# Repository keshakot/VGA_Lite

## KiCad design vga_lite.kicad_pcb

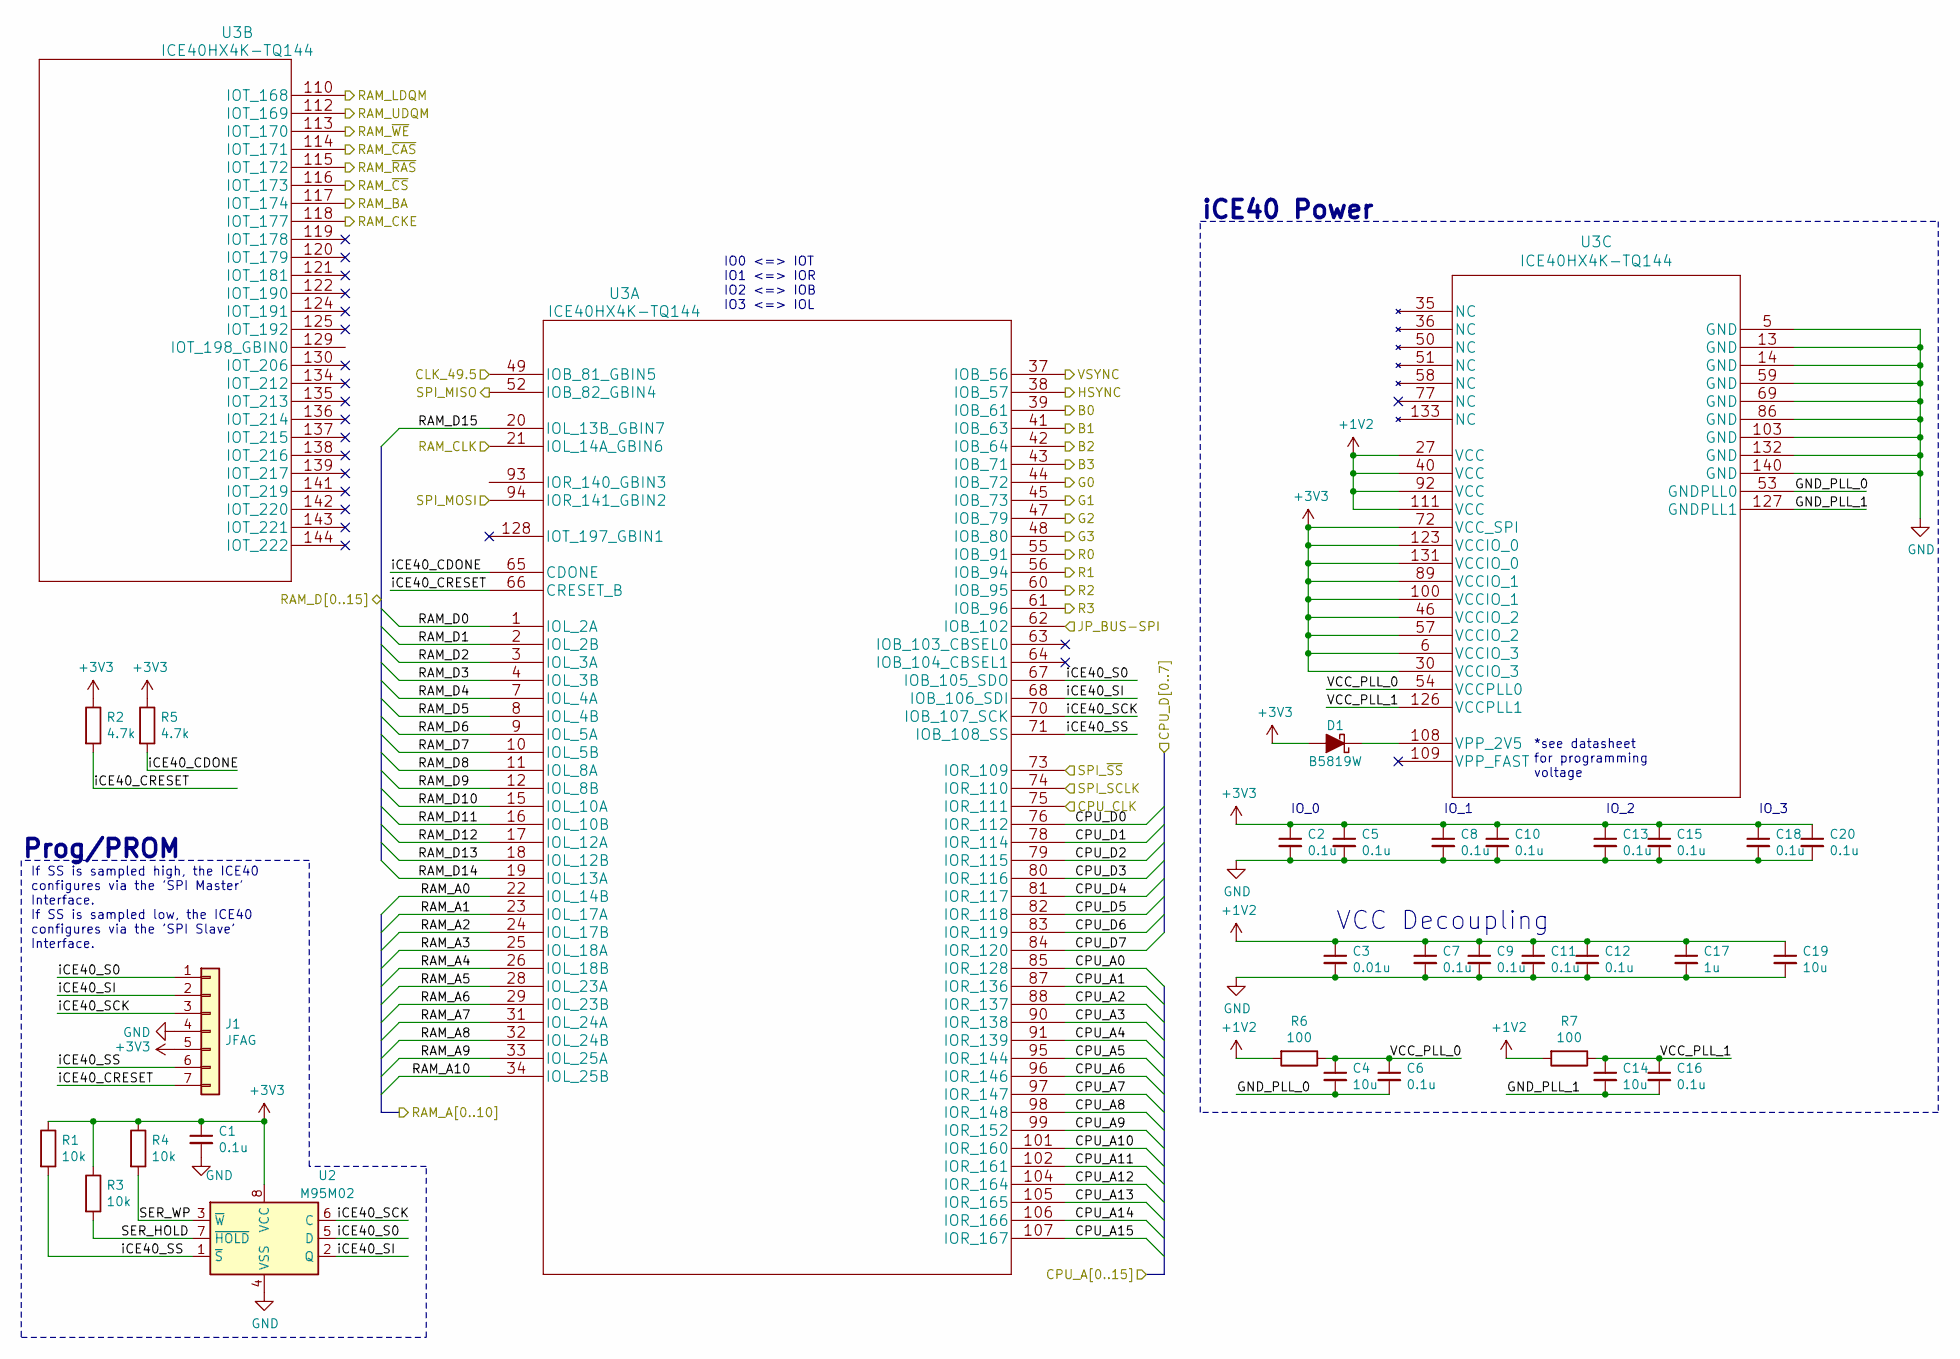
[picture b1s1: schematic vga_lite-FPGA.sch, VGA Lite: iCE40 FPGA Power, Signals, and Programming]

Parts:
C1, C2, C5, C6, C7, C8, C9, C10, C11, C12, C13, C15, C16, C18, C20: 0.1u; C_0402_1005Metric
C3: 0.01u; C_0402_1005Metric
C4, C14, C19: 10u; C_0402_1005Metric
C17: 1u; C_0402_1005Metric
D1: B5819W; D_SOD-123
J1: JFAG; PinHeader_1x07_P2.54mm_Vertical
R1, R3, R4: 10k; R_0402_1005Metric
R2, R5: 4.7k; R_0402_1005Metric
R6, R7: 100; R_0402_1005Metric
U2: M95M02; SOIC-8_3.9x4.9mm_P1.27mm
U3: ICE40HX4K-TQ144; TQFP-144_20x20mm_P0.5mm

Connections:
+1V2: C3.1, C7.1, C9.1, C11.1, C12.1, C17.1, C19.1, R6.2, R7.2, U3.27 (VCC), U3.40 (VCC), U3.92 (VCC), U3.111 (VCC); also elsewhere on the board
/FPGA/B0: U3.39 (IOB_61); also elsewhere on the board
/FPGA/B1: U3.41 (IOB_63); also elsewhere on the board
/FPGA/B2: U3.42 (IOB_64); also elsewhere on the board
/FPGA/B3: U3.43 (IOB_71); also elsewhere on the board
/FPGA/CLK_49.5: U3.49 (IOB_81_GBIN5); also elsewhere on the board
/FPGA/CPU_A0: U3.85 (IOR_128); also elsewhere on the board
/FPGA/CPU_A1: U3.87 (IOR_136); also elsewhere on the board
/FPGA/CPU_A2: U3.88 (IOR_137); also elsewhere on the board
/FPGA/CPU_A3: U3.90 (IOR_138); also elsewhere on the board
/FPGA/CPU_A4: U3.91 (IOR_139); also elsewhere on the board
/FPGA/CPU_A5: U3.95 (IOR_144); also elsewhere on the board
/FPGA/CPU_A6: U3.96 (IOR_146); also elsewhere on the board
/FPGA/CPU_A7: U3.97 (IOR_147); also elsewhere on the board
/FPGA/CPU_A8: U3.98 (IOR_148); also elsewhere on the board
/FPGA/CPU_A9: U3.99 (IOR_152); also elsewhere on the board
/FPGA/CPU_A10: U3.101 (IOR_160); also elsewhere on the board
/FPGA/CPU_A11: U3.102 (IOR_161); also elsewhere on the board
/FPGA/CPU_A12: U3.104 (IOR_164); also elsewhere on the board
/FPGA/CPU_A13: U3.105 (IOR_165); also elsewhere on the board
/FPGA/CPU_A14: U3.106 (IOR_166); also elsewhere on the board
/FPGA/CPU_A15: U3.107 (IOR_167); also elsewhere on the board
/FPGA/CPU_CLK: U3.75 (IOR_111); also elsewhere on the board
/FPGA/CPU_D0: U3.76 (IOR_112); also elsewhere on the board
/FPGA/CPU_D1: U3.78 (IOR_114); also elsewhere on the board
/FPGA/CPU_D2: U3.79 (IOR_115); also elsewhere on the board
/FPGA/CPU_D3: U3.80 (IOR_116); also elsewhere on the board
/FPGA/CPU_D4: U3.81 (IOR_117); also elsewhere on the board
/FPGA/CPU_D5: U3.82 (IOR_118); also elsewhere on the board
/FPGA/CPU_D6: U3.83 (IOR_119); also elsewhere on the board
/FPGA/CPU_D7: U3.84 (IOR_120); also elsewhere on the board
/FPGA/G0: U3.44 (IOB_72); also elsewhere on the board
/FPGA/G1: U3.45 (IOB_73); also elsewhere on the board
/FPGA/G2: U3.47 (IOB_79); also elsewhere on the board
/FPGA/G3: U3.48 (IOB_80); also elsewhere on the board
/FPGA/GND_PLL_0: C4.2, C6.2, U3.53 (GNDPLL0)
/FPGA/GND_PLL_1: C14.2, C16.2, U3.127 (GNDPLL1)
/FPGA/HSYNC: U3.38 (IOB_57); also elsewhere on the board
/FPGA/JP_BUS-SPI: U3.62 (IOB_102); also elsewhere on the board
/FPGA/R0: U3.55 (IOB_91); also elsewhere on the board
/FPGA/R1: U3.56 (IOB_94); also elsewhere on the board
/FPGA/R2: U3.60 (IOB_95); also elsewhere on the board
/FPGA/R3: U3.61 (IOB_96); also elsewhere on the board
/FPGA/RAM_A0: U3.22 (IOL_14B); also elsewhere on the board
/FPGA/RAM_A1: U3.23 (IOL_17A); also elsewhere on the board
/FPGA/RAM_A2: U3.24 (IOL_17B); also elsewhere on the board
/FPGA/RAM_A3: U3.25 (IOL_18A); also elsewhere on the board
/FPGA/RAM_A4: U3.26 (IOL_18B); also elsewhere on the board
/FPGA/RAM_A5: U3.28 (IOL_23A); also elsewhere on the board
/FPGA/RAM_A6: U3.29 (IOL_23B); also elsewhere on the board
/FPGA/RAM_A7: U3.31 (IOL_24A); also elsewhere on the board
/FPGA/RAM_A8: U3.32 (IOL_24B); also elsewhere on the board
/FPGA/RAM_A9: U3.33 (IOL_25A); also elsewhere on the board
/FPGA/RAM_A10: U3.34 (IOL_25B); also elsewhere on the board
/FPGA/RAM_BA: U3.117 (IOT_174); also elsewhere on the board
/FPGA/RAM_CKE: U3.118 (IOT_177); also elsewhere on the board
/FPGA/RAM_CLK: U3.21 (IOL_14A_GBIN6); also elsewhere on the board
/FPGA/RAM_D0: U3.1 (IOL_2A); also elsewhere on the board
/FPGA/RAM_D1: U3.2 (IOL_2B); also elsewhere on the board
/FPGA/RAM_D2: U3.3 (IOL_3A); also elsewhere on the board
/FPGA/RAM_D3: U3.4 (IOL_3B); also elsewhere on the board
/FPGA/RAM_D4: U3.7 (IOL_4A); also elsewhere on the board
/FPGA/RAM_D5: U3.8 (IOL_4B); also elsewhere on the board
/FPGA/RAM_D6: U3.9 (IOL_5A); also elsewhere on the board
/FPGA/RAM_D7: U3.10 (IOL_5B); also elsewhere on the board
/FPGA/RAM_D8: U3.11 (IOL_8A); also elsewhere on the board
/FPGA/RAM_D9: U3.12 (IOL_8B); also elsewhere on the board
/FPGA/RAM_D10: U3.15 (IOL_10A); also elsewhere on the board
/FPGA/RAM_D11: U3.16 (IOL_10B); also elsewhere on the board
/FPGA/RAM_D12: U3.17 (IOL_12A); also elsewhere on the board
/FPGA/RAM_D13: U3.18 (IOL_12B); also elsewhere on the board
/FPGA/RAM_D14: U3.19 (IOL_13A); also elsewhere on the board
/FPGA/RAM_D15: U3.20 (IOL_13B_GBIN7); also elsewhere on the board
/FPGA/RAM_LDQM: U3.110 (IOT_168); also elsewhere on the board
/FPGA/RAM_UDQM: U3.112 (IOT_169); also elsewhere on the board
/FPGA/RAM_~CAS: U3.114 (IOT_171); also elsewhere on the board
/FPGA/RAM_~CS: U3.116 (IOT_173); also elsewhere on the board
/FPGA/RAM_~RAS: U3.115 (IOT_172); also elsewhere on the board
/FPGA/RAM_~WE: U3.113 (IOT_170); also elsewhere on the board
/FPGA/SER_HOLD: R3.2, U2.7 (~HOLD)
/FPGA/SER_WP: R4.2, U2.3 (~W)
/FPGA/SPI_MISO: U3.52 (IOB_82_GBIN4); also elsewhere on the board
/FPGA/SPI_MOSI: U3.94 (IOR_141_GBIN2); also elsewhere on the board
/FPGA/SPI_SCLK: U3.74 (IOR_110); also elsewhere on the board
/FPGA/SPI_~SS: U3.73 (IOR_109); also elsewhere on the board
/FPGA/VCC_PLL_0: C4.1, C6.1, R6.1, U3.54 (VCCPLL0)
/FPGA/VCC_PLL_1: C14.1, C16.1, R7.1, U3.126 (VCCPLL1)
/FPGA/VSYNC: U3.37 (IOB_56); also elsewhere on the board
/FPGA/iCE40_CDONE: R5.2, U3.65 (CDONE)
/FPGA/iCE40_CRESET: J1.7, R2.2, U3.66 (CRESET_B)
/FPGA/iCE40_S0: J1.1, U2.5 (D), U3.67 (IOB_105_SDO)
/FPGA/iCE40_SCK: J1.3, U2.6 (C), U3.70 (IOB_107_SCK)
/FPGA/iCE40_SI: J1.2, U2.2 (Q), U3.68 (IOB_106_SDI)
/FPGA/iCE40_SS: J1.6, R1.2, U2.1 (~S), U3.71 (IOB_108_SS)
GND: C1.2, C2.2, C3.2, C5.2, C7.2, C8.2, C9.2, C10.2, C11.2, C12.2, C13.2, C15.2, C17.2, C18.2, C19.2, C20.2, J1.4, U2.4 (VSS), U3.5 (GND), U3.13 (GND), U3.14 (GND), U3.59 (GND), U3.69 (GND), U3.86 (GND), U3.103 (GND), U3.132 (GND), U3.140 (GND); also elsewhere on the board
unnamed: D1.1 (K), U3.108 (VPP_2V5)

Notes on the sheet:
IO_0
IO_1
IO_2
IO_3
*see datasheet for programming voltage
VCC Decoupling
If SS is sampled high, the ICE40 configures via the 'SPI Master' Interface. If SS is sampled low, the ICE40 configures via the 'SPI Slave' Interface.
Prog/PROM
iCE40 Power
IO0 <=> IOT IO1 <=> IOR IO2 <=> IOB IO3 <=> IOL

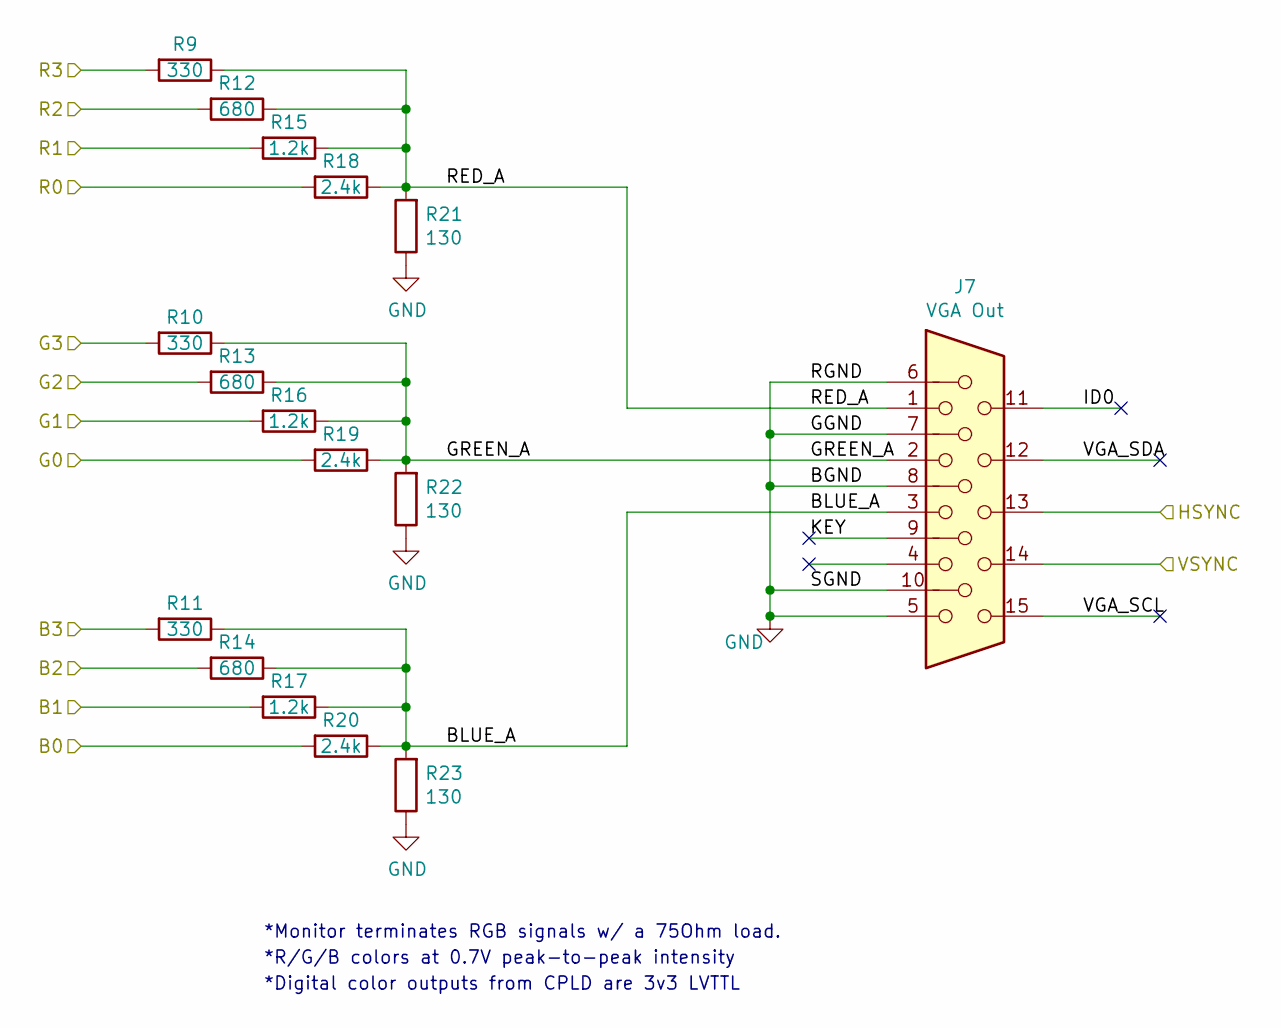
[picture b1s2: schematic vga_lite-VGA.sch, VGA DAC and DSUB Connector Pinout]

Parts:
J7: VGA Out; DSUB-15-HD_Female_Horizontal_P2.29x1.98mm_EdgePinOffset8.35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
R9, R10, R11: 330; R_0402_1005Metric
R12, R13, R14: 680; R_0402_1005Metric
R15, R16, R17: 1.2k; R_0402_1005Metric
R18, R19, R20: 2.4k; R_0402_1005Metric
R21, R22, R23: 130; R_0402_1005Metric

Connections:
/FPGA/B0: R20.2; also elsewhere on the board
/FPGA/B1: R17.2; also elsewhere on the board
/FPGA/B2: R14.2; also elsewhere on the board
/FPGA/B3: R11.2; also elsewhere on the board
/FPGA/G0: R19.2; also elsewhere on the board
/FPGA/G1: R16.2; also elsewhere on the board
/FPGA/G2: R13.2; also elsewhere on the board
/FPGA/G3: R10.2; also elsewhere on the board
/FPGA/HSYNC: J7.13; also elsewhere on the board
/FPGA/R0: R18.2; also elsewhere on the board
/FPGA/R1: R15.2; also elsewhere on the board
/FPGA/R2: R12.2; also elsewhere on the board
/FPGA/R3: R9.2; also elsewhere on the board
/FPGA/VSYNC: J7.14; also elsewhere on the board
/VGA/BLUE_A: J7.3, R11.1, R14.1, R17.1, R20.1, R23.2
/VGA/GREEN_A: J7.2, R10.1, R13.1, R16.1, R19.1, R22.2
/VGA/ID0: J7.11
/VGA/KEY: J7.9
/VGA/RED_A: J7.1, R9.1, R12.1, R15.1, R18.1, R21.2
/VGA/VGA_SCL: J7.15
/VGA/VGA_SDA: J7.12
GND: J7.5, J7.6, J7.7, J7.8, J7.10, R21.1, R22.1, R23.1; also elsewhere on the board

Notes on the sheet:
*Monitor terminates RGB signals w/ a 75Ohm load.
*Digital color outputs from CPLD are 3v3 LVTTL
*R/G/B colors at 0.7V peak-to-peak intensity

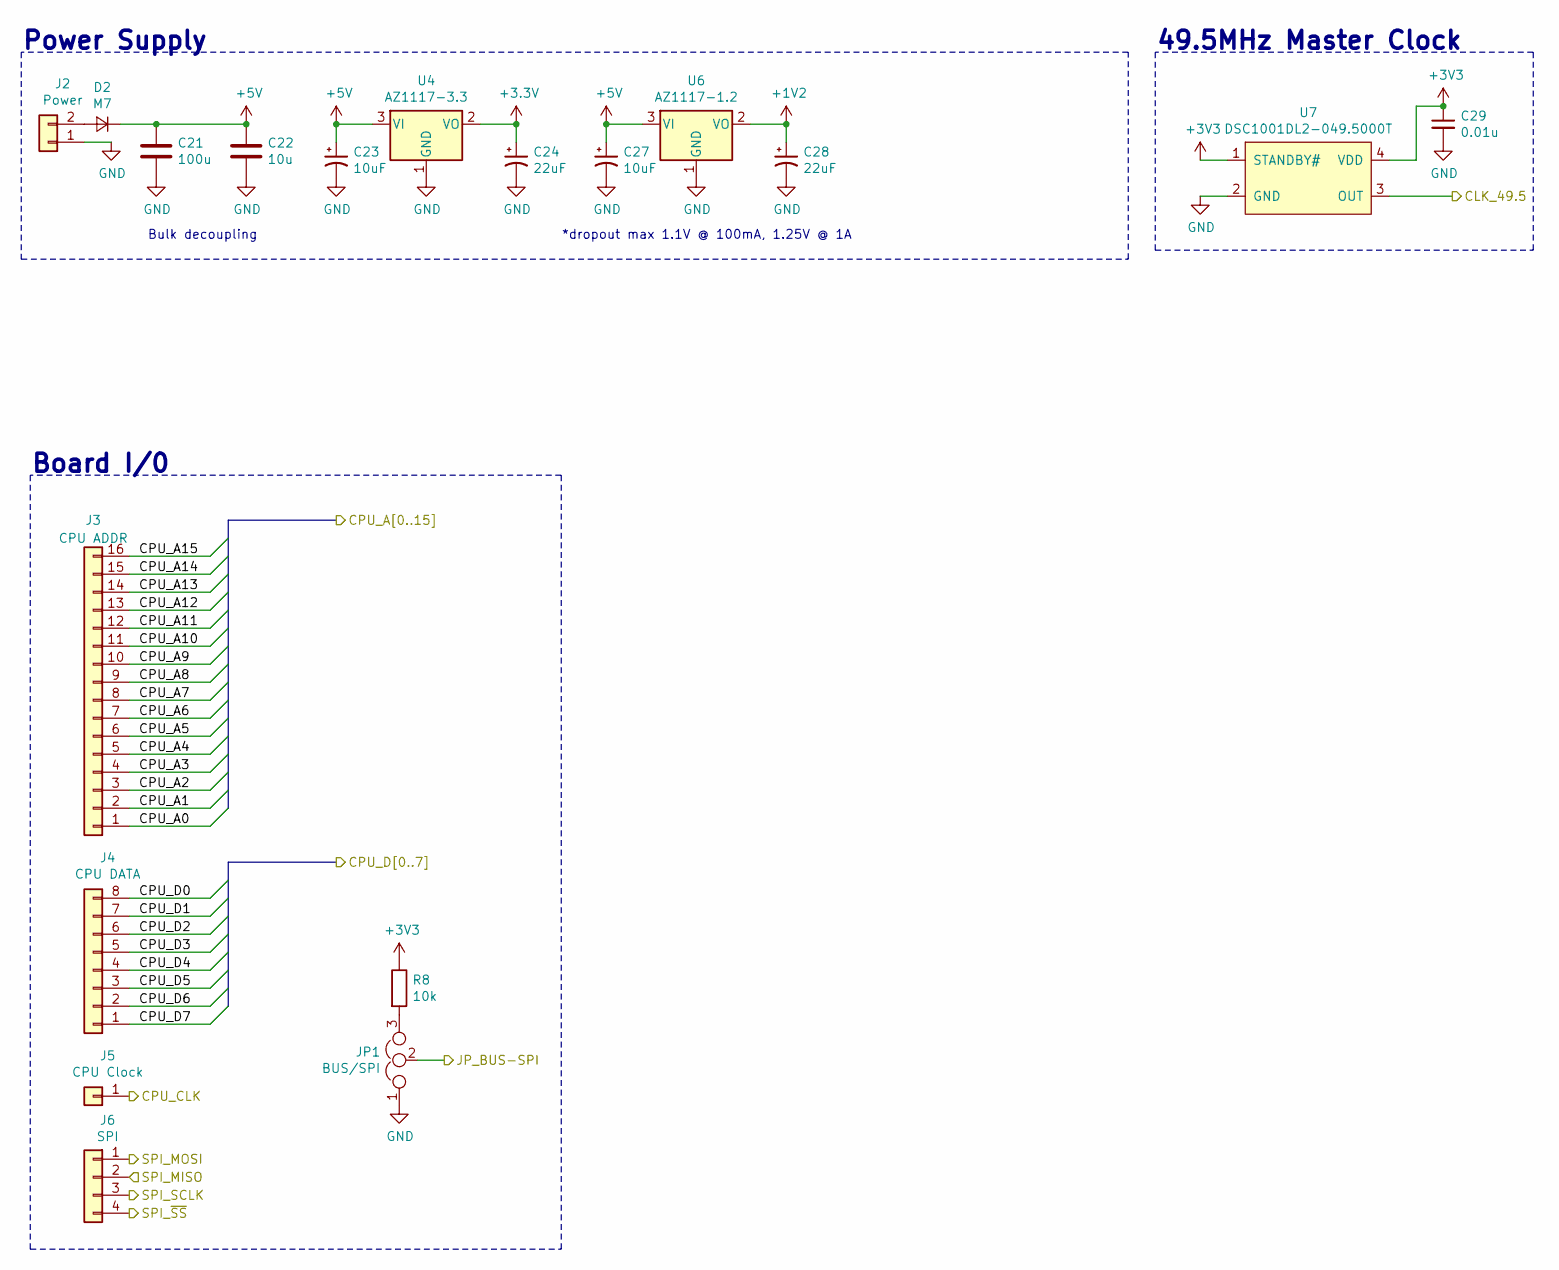
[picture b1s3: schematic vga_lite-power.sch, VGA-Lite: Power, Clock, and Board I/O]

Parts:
C21: 100u; C_0603_1608Metric
C22: 10u; C_0603_1608Metric
C23, C27: 10uF; CP_EIA-3216-10_Kemet-I
C24, C28: 22uF; CP_EIA-3216-10_Kemet-I
C29: 0.01u; C_0402_1005Metric
D2: M7; D_SMA
J2: Power; PinHeader_1x02_P2.54mm_Vertical
J3: CPU ADDR; PinHeader_1x16_P2.54mm_Vertical
J4: CPU DATA; PinHeader_1x08_P2.54mm_Vertical
J5: CPU Clock; PinHeader_1x01_P2.54mm_Vertical
J6: SPI; PinHeader_1x04_P2.54mm_Vertical
JP1: BUS/SPI; PinHeader_1x03_P2.54mm_Vertical
R8: 10k; R_0402_1005Metric
U4: AZ1117-3.3; SOT-223-3_TabPin2
U6: AZ1117-1.2; SOT-223-3_TabPin2
U7: DSC1001DL2-049.5000T; OSCDFN250X200X89-4N

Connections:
+1V2: C28.1, U6.2 (VO); also elsewhere on the board
+5V: C21.1, C22.1, C23.1, C27.1, D2.1 (K), U4.3 (VI), U6.3 (VI)
/FPGA/CLK_49.5: U7.3 (OUT); also elsewhere on the board
/FPGA/CPU_A0: J3.1; also elsewhere on the board
/FPGA/CPU_A1: J3.2; also elsewhere on the board
/FPGA/CPU_A2: J3.3; also elsewhere on the board
/FPGA/CPU_A3: J3.4; also elsewhere on the board
/FPGA/CPU_A4: J3.5; also elsewhere on the board
/FPGA/CPU_A5: J3.6; also elsewhere on the board
/FPGA/CPU_A6: J3.7; also elsewhere on the board
/FPGA/CPU_A7: J3.8; also elsewhere on the board
/FPGA/CPU_A8: J3.9; also elsewhere on the board
/FPGA/CPU_A9: J3.10; also elsewhere on the board
/FPGA/CPU_A10: J3.11; also elsewhere on the board
/FPGA/CPU_A11: J3.12; also elsewhere on the board
/FPGA/CPU_A12: J3.13; also elsewhere on the board
/FPGA/CPU_A13: J3.14; also elsewhere on the board
/FPGA/CPU_A14: J3.15; also elsewhere on the board
/FPGA/CPU_A15: J3.16; also elsewhere on the board
/FPGA/CPU_CLK: J5.1; also elsewhere on the board
/FPGA/CPU_D0: J4.8; also elsewhere on the board
/FPGA/CPU_D1: J4.7; also elsewhere on the board
/FPGA/CPU_D2: J4.6; also elsewhere on the board
/FPGA/CPU_D3: J4.5; also elsewhere on the board
/FPGA/CPU_D4: J4.4; also elsewhere on the board
/FPGA/CPU_D5: J4.3; also elsewhere on the board
/FPGA/CPU_D6: J4.2; also elsewhere on the board
/FPGA/CPU_D7: J4.1; also elsewhere on the board
/FPGA/JP_BUS-SPI: JP1.2; also elsewhere on the board
/FPGA/SPI_MISO: J6.2; also elsewhere on the board
/FPGA/SPI_MOSI: J6.1; also elsewhere on the board
/FPGA/SPI_SCLK: J6.3; also elsewhere on the board
/FPGA/SPI_~SS: J6.4; also elsewhere on the board
GND: C21.2, C22.2, C23.2, C24.2, C27.2, C28.2, C29.2, J2.1, JP1.1, U4.1 (GND), U6.1 (GND), U7.2 (GND); also elsewhere on the board
unnamed: D2.2 (A), J2.2
unnamed: JP1.3, R8.2

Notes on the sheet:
Bulk decoupling
*dropout max 1.1V @ 100mA, 1.25V @ 1A
49.5MHz Master Clock
Power Supply
Board I/0

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
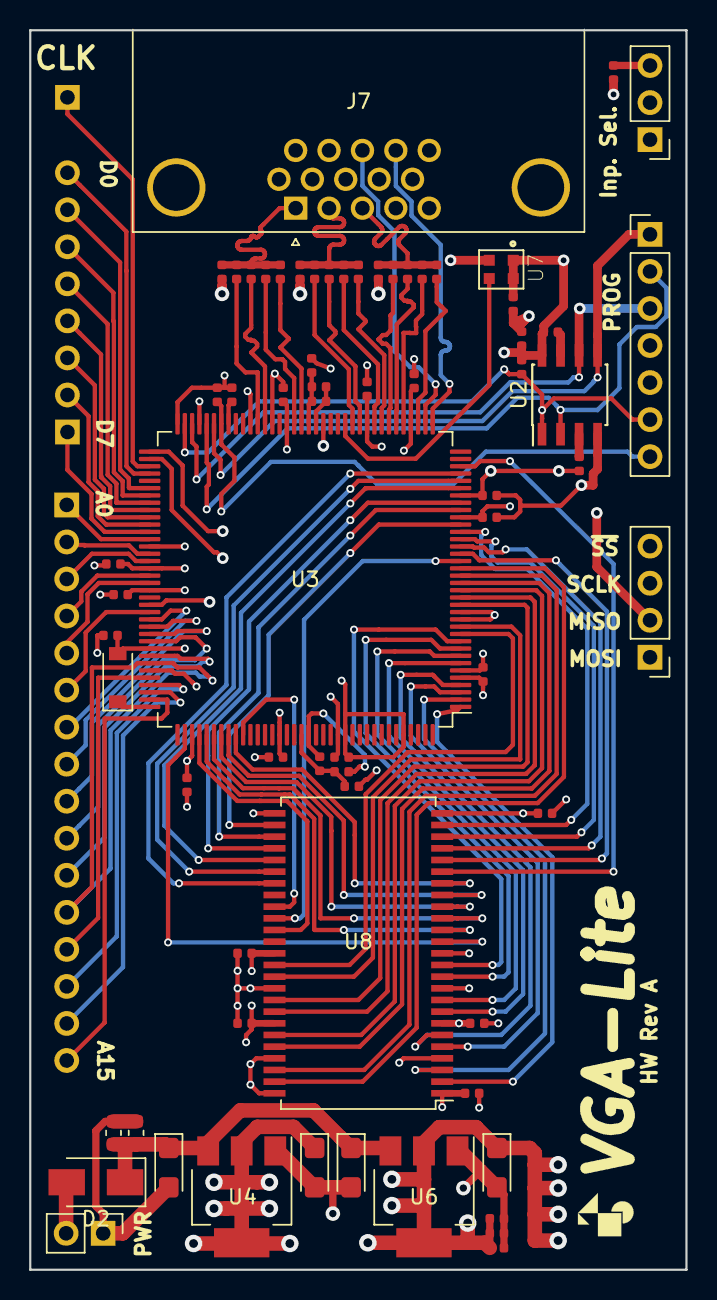
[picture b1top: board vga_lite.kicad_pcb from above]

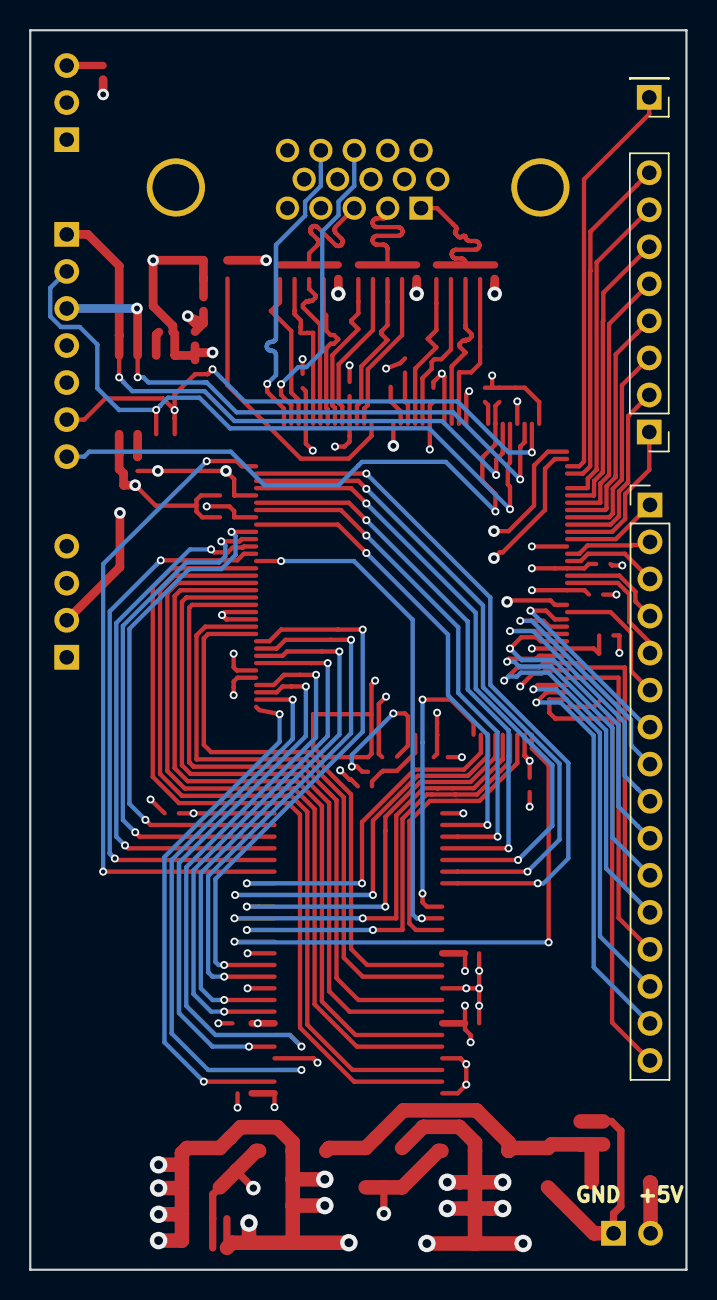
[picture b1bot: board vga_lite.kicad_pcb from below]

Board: 6 copper layers, 45.0 x 85.0 mm, 71 parts (3 on the bottom side), 103 nets.

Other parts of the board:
C30, C31, C32, C33, C34: 0.1u; C_0402_1005Metric
U8: W9816G6JH-6; TSOP-II-50_21.1x10.16mm_P0.8mm

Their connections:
/FPGA/RAM_A0: U8.21; also elsewhere on the board
/FPGA/RAM_A1: U8.22; also elsewhere on the board
/FPGA/RAM_A2: U8.23; also elsewhere on the board
/FPGA/RAM_A3: U8.24; also elsewhere on the board
/FPGA/RAM_A4: U8.27; also elsewhere on the board
/FPGA/RAM_A5: U8.28; also elsewhere on the board
/FPGA/RAM_A6: U8.29; also elsewhere on the board
/FPGA/RAM_A7: U8.30; also elsewhere on the board
/FPGA/RAM_A8: U8.31; also elsewhere on the board
/FPGA/RAM_A9: U8.32; also elsewhere on the board
/FPGA/RAM_A10: U8.20; also elsewhere on the board
/FPGA/RAM_BA: U8.19; also elsewhere on the board
/FPGA/RAM_CKE: U8.34; also elsewhere on the board
/FPGA/RAM_CLK: U8.35; also elsewhere on the board
/FPGA/RAM_D0: U8.2; also elsewhere on the board
/FPGA/RAM_D1: U8.3; also elsewhere on the board
/FPGA/RAM_D2: U8.5; also elsewhere on the board
/FPGA/RAM_D3: U8.6; also elsewhere on the board
/FPGA/RAM_D4: U8.8; also elsewhere on the board
/FPGA/RAM_D5: U8.9; also elsewhere on the board
/FPGA/RAM_D6: U8.11; also elsewhere on the board
/FPGA/RAM_D7: U8.12; also elsewhere on the board
/FPGA/RAM_D8: U8.39; also elsewhere on the board
/FPGA/RAM_D9: U8.40; also elsewhere on the board
/FPGA/RAM_D10: U8.42; also elsewhere on the board
/FPGA/RAM_D11: U8.43; also elsewhere on the board
/FPGA/RAM_D12: U8.45; also elsewhere on the board
/FPGA/RAM_D13: U8.46; also elsewhere on the board
/FPGA/RAM_D14: U8.48; also elsewhere on the board
/FPGA/RAM_D15: U8.49; also elsewhere on the board
/FPGA/RAM_LDQM: U8.14; also elsewhere on the board
/FPGA/RAM_UDQM: U8.36; also elsewhere on the board
/FPGA/RAM_~CAS: U8.16; also elsewhere on the board
/FPGA/RAM_~CS: U8.18; also elsewhere on the board
/FPGA/RAM_~RAS: U8.17; also elsewhere on the board
/FPGA/RAM_~WE: U8.15; also elsewhere on the board
GND: C30.2, C31.2, C32.2, C33.2, C34.2, U8.4, U8.10, U8.13, U8.26, U8.41, U8.47, U8.50; also elsewhere on the board

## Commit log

2020-08-26 Schematic added
2020-08-27 Added KiCad design files
2020-08-28 Added PCB image
